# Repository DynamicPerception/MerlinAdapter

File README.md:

Merlin Adapter
==============

PCB for interfacing TTL serial device, such as the MX2 to the Merlin-style Telescope heads.

For more information, see: http://dynamicperception.com/products/merlin-adapter-kit-mx2

License and Copyright
---------------------

The Merlin Adapter is Copyright (c) 2010-2013 Dynamic Perception LLC.

All files shared under the Creative Commons Attibution-Share-Alike 3.0 License.

The MX2 name is a trademark of Dynamic Perception LLC.

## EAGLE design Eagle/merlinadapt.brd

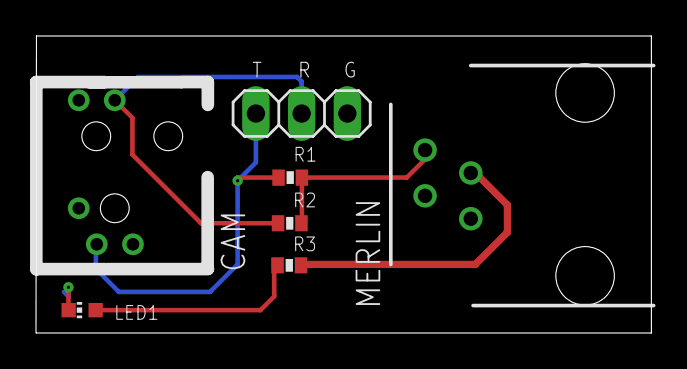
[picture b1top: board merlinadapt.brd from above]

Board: 2 copper layers, 34.2 x 16.5 mm, 7 parts (0 on the bottom side), 6 nets.

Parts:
CAM: 161-2508-EXTHRU-HOLE-PCB-RA; PCB-HORIZ
JP1: 1X03
LED1: CHIP-LED0603
MERLIN: 5555165-2-6.4RT; CONNMODJACK
R1, R2: 220; 0402-RES
R3: 120k; 0402-RES

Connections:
COM: MERLIN.4, R1.2, R2.2
GND: CAM.1, JP1.3, LED1.C, MERLIN.1
unnamed: LED1.A, R3.1
RX: CAM.4, JP1.2, R2.1
TX: CAM.2, JP1.1, R1.1
VCC: MERLIN.3, R3.2

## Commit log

2013-03-27 * Added Required Files
2013-03-28 * Added to README
